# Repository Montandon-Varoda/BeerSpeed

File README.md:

# BeerSpeed
Who's going to drink it the fastest ?

## Documentation
Toute la documentation se trouve sur le [wiki](https://github.com/Montandon-Varoda/BeerSpeed/wiki)

## Description

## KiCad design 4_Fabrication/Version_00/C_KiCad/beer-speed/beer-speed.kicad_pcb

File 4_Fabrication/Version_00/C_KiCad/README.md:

## Ajout des plugins KiCad

`
les plugin se trouve sur le gitlab de l'atelier ELO (privé)
`

Copier fichier scripting qui se trouve dans:</br>
KiCAD\Librairies\KICAD_LIB\_Plugins\CpyNexttoAppdataKicad</br>
Le Coller dans:</br>
C:\Users\NOM_PC\AppData\Roaming\kicad</br>
Puis ouvrir Kicad sur PCB aller dans l'onglet outil puis Plugin et rafraichir.

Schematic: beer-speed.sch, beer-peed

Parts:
BT1: Battery_Cell; BS-7-ND-20mm
C1, C2: 16 pF; C_0805_2012Metric
H1, H2, H3, H4: MountingHole; MountingHole_3.2mm_M3
J1: Conn_02x03_Odd_Even; PinHeader_2x03_P2.54mm_Vertical
NT1: Net-Tie_2; NetTie-2_SMD_Pad2.0mm
P1: LCD-S401C52TR
R1: 10K; R_1206_3216Metric
SW1: EG1213
SW2: TM1000Q
U1: ATmega4809-A; TQFP-48_7x7mm_P0.5mm
Y1: Crystal 8MHz; Crystal_SMD_HC49-SD_HandSoldering

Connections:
1A: P1.35 (1A), U1.44 (PA0)
1B: P1.34 (1B), U1.45 (PA1)
1C: P1.7 (1C), U1.46 (PA2)
1D: P1.6 (1D), U1.47 (PA3)
1E: J1.4, P1.5 (1E), U1.48 (PA4)
1F: J1.1, P1.36 (1F), U1.1 (PA5)
1G: J1.3, P1.37 (1G), U1.2 (PA6)
2A: P1.30 (2A), U1.3 (PA7)
2B: P1.29 (2B), U1.4 (PB0)
2C: P1.11 (2C), U1.5 (PB1)
2D: P1.10 (2D), U1.6 (PB2)
2E: P1.9 (2E), U1.7 (PB3)
2F: P1.31 (2F), U1.8 (PB4)
2G: P1.32 (2G), U1.9 (PB5)
3A: P1.25 (3A), U1.10 (PC0)
3B: P1.24 (3B), U1.11 (PC1)
3C: P1.15 (3C), U1.12 (PC2)
3D: P1.14 (3D), U1.13 (PC3)
3E: P1.13 (3E), U1.16 (PC4)
3F: P1.26 (3F), U1.17 (PC5)
3G: P1.27 (3G), U1.18 (PC6)
4A: P1.21 (4A), U1.20 (PD0)
4B: P1.20 (4B), U1.21 (PD1)
4C: P1.19 (4C), U1.22 (PD2)
4D: P1.18 (4D), U1.23 (PD3)
4E: P1.17 (4E), U1.24 (PD4)
4F: P1.22 (4F), U1.25 (PD5)
4G: P1.23 (4G), U1.26 (PD6)
+3V0: J1.2, R1.1, SW1.1 (A), SW2.2 (B), U1.14 (VCC), U1.42 (VCC)
COL: P1.28 (COL), U1.30 (PE0)
DP1: P1.8 (DP1), U1.31 (PE1)
DP2: P1.12 (DP2), U1.32 (PE2)
DP3: P1.16 (DP3), U1.33 (PE3)
GND: BT1.2 (-), J1.6, NT1.2, P1.1 (COM), P1.40 (COM), U1.15 (GND), U1.29 (GND), U1.43 (GND)
unnamed: BT1.1 (+), SW1.2 (B)
unnamed: C1.1, C2.2, NT1.1
unnamed: C1.2, U1.34 (PF0), Y1.2
unnamed: C2.1, U1.35 (PF1), Y1.1
unnamed: SW2.1 (A), SW2.3 (C), U1.19 (PC7)
RESET: J1.5, R1.2, U1.40 (PF6/~RESET)

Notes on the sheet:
MOSI
MISO
SCK
Alimentation
Pile CR 2032 (20 mm) || 3V
Affichage
LCD 4 digit || 8 . 8 . : 8 . 8
Programmation
Conecteur 2x3 programation spi
Atmega
BeerSpeed
trou de fixation

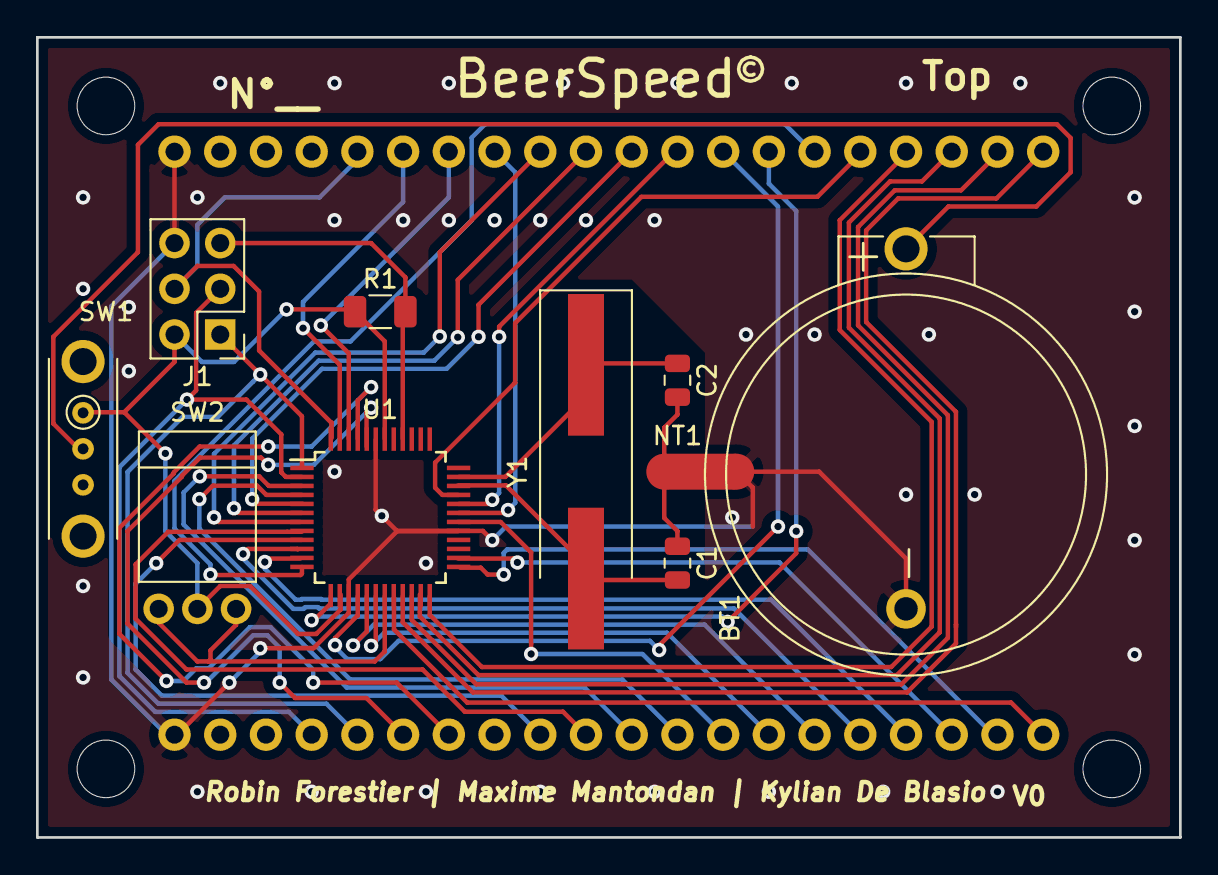
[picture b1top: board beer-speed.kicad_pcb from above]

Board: 2 copper layers, 63.5 x 44.5 mm, 15 parts (1 on the bottom side), 40 nets.

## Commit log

2021-05-09 first commit
    Creation of folder.
2021-05-09 add excel composant
    - Excel composant
    - DataSheet
2021-05-09 Create Shema_block_v0.png
    creat rhe first idea of the circuit.
2021-05-10 add datasheet
    add datasheet
    modif excel
2021-05-10 first kicad
2021-05-11 modif kicad
    add prog connector
2021-05-11 modif kicad
    small modif
2021-05-11 add footprint
    add footprint
    add designation
    creat footprint EG1213
    add 3d to EG1213
2021-05-11 modif kicad
    modif kicad
    modif datasheet
    add 3d
    add screen footprint
    add sensor footprint
2021-05-11 merde
2021-05-11 creat PCB v0
    creat PCB
    add archive
2021-05-11 plugin
2021-05-11 add plugin
    add plugin
2021-05-11 plug in
2021-05-11 modif name
2021-05-11 name
2021-05-11 datasheet
2021-05-12 first placement
    first placement on KiaCad PCB
2021-05-12 KiCad PCB V0
    First version of KiCad PCB
2021-05-12 add text on PCB + img
    add TITLE on PCB
    add name on PCB
    add 2 img of 3d PCB on 1_DOCUMENTATION
